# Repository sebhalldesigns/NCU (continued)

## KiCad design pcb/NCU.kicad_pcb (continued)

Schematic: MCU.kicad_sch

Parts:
C89: 100nF; C_0603_1608Metric_Pad1.08x0.95mm_HandSolder
C90, C92: 8.2pF; C_0603_1608Metric_Pad1.08x0.95mm_HandSolder
C91, C93: 5.1pF; C_0603_1608Metric_Pad1.08x0.95mm_HandSolder
D26: LED; LED_0603_1608Metric_Pad1.05x0.95mm_HandSolder
D27: SP0504BAHT; SOT-23-5
JP12: SolderJumper_2_Open; SolderJumper-2_P1.3mm_Open_RoundedPad1.0x1.5mm
R123, R125, R126: 10k; R_0603_1608Metric_Pad0.98x0.95mm_HandSolder
R124: 260R; R_0603_1608Metric_Pad0.98x0.95mm_HandSolder
TP18: BOOT; TestPoint_THTPad_D2.0mm_Drill1.0mm
U7: STM32H745ZITx; LQFP-144_20x20mm_P0.5mm
Y2: NX3215SA-32.768K-STD-MUS-2; NX3215SA32768KSTDMUS2; Mouser Part Number 344-NX3215SA32768K2
Y3: Crystal_GND24; NX2016SA32MEXS00ACS06465

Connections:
3V3: JP12.2 (B), R123.1, R126.1, U7.7 (VDD), U7.8 (VBAT), U7.13 (VDD), U7.16 (VDDSMPS), U7.19 (VDD), U7.32 (VDD), U7.42 (VDD), U7.56 (VDD), U7.71 (VDD), U7.79 (VDD), U7.90 (VDD50_USB), U7.91 (VDD33_USB), U7.92 (VDD), U7.106 (VDD), U7.119 (VDD), U7.129 (VDD), U7.144 (VDD); also elsewhere on the board
/CARD_SD/SD_CD: U7.99 (PA10); also elsewhere on the board
/CARD_SD/SD_CLK: U7.111 (SDMMC1_CK); also elsewhere on the board
/CARD_SD/SD_CMD: U7.114 (SDMMC1_CMD); also elsewhere on the board
/CARD_SD/SD_DAT0: U7.95 (SDMMC1_D0); also elsewhere on the board
/CARD_SD/SD_DAT1: U7.96 (SDMMC1_D1); also elsewhere on the board
/CARD_SD/SD_DAT2: U7.109 (SDMMC1_D2); also elsewhere on the board
/CARD_SD/SD_DAT3: U7.110 (SDMMC1_D3); also elsewhere on the board
/CONN_B/STM_SWDCLK: D27.3 (K), U7.107 (DEBUG_JTCK-SWCLK); also elsewhere on the board
/CONN_B/STM_SWDIO: D27.1 (K), U7.102 (DEBUG_JTMS-SWDIO); also elsewhere on the board
/CONN_B/STM_SWO: D27.5 (K), U7.130 (DEBUG_JTDO-SWO); also elsewhere on the board
/CONN_B/STM_USB_DM: U7.100 (USB_OTG_FS_DM); also elsewhere on the board
/CONN_B/STM_USB_DP: U7.101 (USB_OTG_FS_DP); also elsewhere on the board
/DRIVES/HSD0_CTRL: U7.82 (TIM4_CH1); also elsewhere on the board
/DRIVES/HSD1_CTRL: U7.83 (TIM4_CH2); also elsewhere on the board
/DRIVES/HSD01_EN: U7.81 (PD11); also elsewhere on the board
/DRIVES/HSD01_ISEN: U7.20 (ADC3_INP8); also elsewhere on the board
/DRIVES/HSD01_SEL: U7.21 (PF7); also elsewhere on the board
/DRIVES/HSD2_CTRL: U7.136 (TIM4_CH3); also elsewhere on the board
/DRIVES/HSD3_CTRL: U7.137 (TIM4_CH4); also elsewhere on the board
/DRIVES/HSD23_EN: U7.134 (PB7); also elsewhere on the board
/DRIVES/HSD23_ISEN: U7.22 (ADC3_INP7); also elsewhere on the board
/DRIVES/HSD23_SEL: U7.23 (PF9); also elsewhere on the board
/DRIVES/LSD0_CTRL: U7.59 (TIM1_CH1); also elsewhere on the board
/DRIVES/LSD0_STAT: U7.60 (PE10); also elsewhere on the board
/DRIVES/LSD1_CTRL: U7.61 (TIM1_CH2); also elsewhere on the board
/DRIVES/LSD1_STAT: U7.62 (PE12); also elsewhere on the board
/DRIVES/LSD2_CTRL: U7.63 (TIM1_CH3); also elsewhere on the board
/DRIVES/LSD2_STAT: U7.57 (PE7); also elsewhere on the board
/DRIVES/LSD3_CTRL: U7.64 (TIM1_CH4); also elsewhere on the board
/DRIVES/LSD3_STAT: U7.58 (PE8); also elsewhere on the board
/GPIO/GPIO0_IO: U7.43 (DAC1_OUT1); also elsewhere on the board
/GPIO/GPIO1_IO: U7.44 (DAC1_OUT2); also elsewhere on the board
/GPIO/GPIO2_IO: U7.37 (ADC1_INP16); also elsewhere on the board
/GPIO/GPIO3_IO: U7.38 (ADC1_INP17); also elsewhere on the board
/INPUTS/AIN0_IO: U7.40 (ADC1_INP15); also elsewhere on the board
/INPUTS/AIN1_IO: U7.45 (ADC1_INP3); also elsewhere on the board
/INPUTS/AIN2_IO: U7.50 (ADC1_INP5); also elsewhere on the board
/INPUTS/AIN3_IO: U7.28 (ADC1_INP10); also elsewhere on the board
/INPUTS/DIN0_IO: U7.30 (ADC3_INP0); also elsewhere on the board
/INPUTS/DIN1_IO: U7.31 (ADC3_INP1); also elsewhere on the board
/INPUTS/DIN2_IO: U7.24 (ADC3_INN2); also elsewhere on the board
/INPUTS/DIN3_IO: U7.52 (ADC1_INP2); also elsewhere on the board
/MCU/3V3_PG: U7.116 (PD4); also elsewhere on the board
/MCU/12V_IO: U7.53 (ADC2_INP6)
/MCU/A5V_PG: U7.117 (PD5); also elsewhere on the board
/MCU/CAN0_RX: U7.112 (FDCAN1_RX); also elsewhere on the board
/MCU/CAN0_TX: U7.113 (FDCAN1_TX); also elsewhere on the board
/MCU/CAN1_RX: U7.132 (FDCAN2_RX); also elsewhere on the board
/MCU/CAN1_TX: U7.133 (FDCAN2_TX); also elsewhere on the board
/MCU/ESP_SPI_CLK: U7.1 (SPI4_SCK); also elsewhere on the board
/MCU/ESP_SPI_CS: U7.3 (SPI4_NSS); also elsewhere on the board
/MCU/ESP_SPI_MISO: U7.4 (SPI4_MISO); also elsewhere on the board
/MCU/ESP_SPI_MOSI: U7.5 (SPI4_MOSI); also elsewhere on the board
/MCU/ETH_CRS_DV: U7.46 (ETH_CRS_DV); also elsewhere on the board
/MCU/ETH_INT: U7.49 (PB0); also elsewhere on the board
/MCU/ETH_MDC: U7.29 (ETH_MDC); also elsewhere on the board
/MCU/ETH_MDIO: U7.39 (ETH_MDIO); also elsewhere on the board
/MCU/ETH_RST: U7.108 (PA15); also elsewhere on the board
/MCU/ETH_RXD0: U7.47 (ETH_RXD0); also elsewhere on the board
/MCU/ETH_RXD1: U7.48 (ETH_RXD1); also elsewhere on the board
/MCU/ETH_TXD0: U7.72 (ETH_TXD0); also elsewhere on the board
/MCU/ETH_TXD1: U7.73 (ETH_TXD1); also elsewhere on the board
/MCU/ETH_TXEN: U7.67 (ETH_TX_EN); also elsewhere on the board
/MCU/LV_PG: U7.115 (PD3); also elsewhere on the board
/MCU/MCU Power/VDDLDO: U7.70 (VDDLDO), U7.105 (VDDLDO), U7.143 (VDDLDO); also elsewhere on the board
/MCU/PCIE_UART_CTS: U7.84 (UART8_CTS); also elsewhere on the board
/MCU/PCIE_UART_RTS: U7.85 (UART8_RTS); also elsewhere on the board
/MCU/PCIE_W_DISABLE: U7.120 (PD6); also elsewhere on the board
/MCU/RCC_OSC32_IN: C93.1, U7.10 (RCC_OSC32_IN), Y2.2
/MCU/RCC_OSC32_OUT: C91.1, U7.11 (RCC_OSC32_OUT), Y2.1
/MCU/RCC_OSC_IN: C92.1, U7.25 (RCC_OSC_IN), Y3.1
/MCU/RCC_OSC_OUT: C90.1, U7.26 (RCC_OSC_OUT), Y3.3
/MCU/STM_NRST: C89.1, D27.4 (K), R123.2, U7.27 (NRST); also elsewhere on the board
/MCU/VCAP: U7.68 (VCAP), U7.103 (VCAP), U7.140 (VCAP); also elsewhere on the board
/MCU/VFBSMPS: U7.17 (VFBSMPS); also elsewhere on the board
/MCU/VLXSMPS: U7.15 (VLXSMPS); also elsewhere on the board
/MCU/VREF+: U7.35 (VREF+), U7.36 (VDDA); also elsewhere on the board
/MOD_PCIE/UART_RX: U7.139 (UART8_TX); also elsewhere on the board
/MOD_PCIE/UART_TX: U7.138 (UART8_RX); also elsewhere on the board
GND: C89.2, C90.2, C91.2, C92.2, C93.2, D26.1 (K), D27.2 (A), R125.2, U7.6 (VSS), U7.12 (VSS), U7.14 (VSSSMPS), U7.18 (VSS), U7.33 (VSS), U7.34 (VSSA), U7.41 (VSS), U7.55 (VSS), U7.69 (VSS), U7.80 (VSS), U7.89 (VSS), U7.104 (VSS), U7.118 (VSS), U7.128 (VSS), U7.141 (VSS), Y3.2, Y3.4; also elsewhere on the board
unnamed: D26.2 (A), R124.2
unnamed: JP12.1 (A), R125.1, TP18.1, U7.135 (BOOT0)
unnamed: R126.2, U7.142 (PDR_ON)
unnamed: R124.1, U7.65 (PE15)
USB_VBUS: U7.98 (USB_OTG_FS_VBUS); also elsewhere on the board

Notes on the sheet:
Solder jumper for boot recovery - bridge to enter system bootloader mode

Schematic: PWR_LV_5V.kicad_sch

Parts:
C73, C74: 4.7uF; C_1210_3225Metric_Pad1.33x2.70mm_HandSolder
C75, C76: 0.1uF; C_0603_1608Metric_Pad1.08x0.95mm_HandSolder
C77: 33pF; C_0603_1608Metric_Pad1.08x0.95mm_HandSolder
C78, C79: 47uF; C_1210_3225Metric_Pad1.33x2.70mm_HandSolder
IC6: LMR51460SQDRRRQ1; SON50P300X300X80-13N-D; Manufacturer_Part_Number LMR51460SQDRRRQ1
L2: 4.7uH; L_Coilcraft_XAL7030-472
NT2: NetTie_2; NetTie-2_SMD_Pad0.5mm
R110: 19.1k; R_0603_1608Metric_Pad0.98x0.95mm_HandSolder
R111, R112: 100k; R_0603_1608Metric_Pad0.98x0.95mm_HandSolder
R113: 1k; R_0603_1608Metric_Pad0.98x0.95mm_HandSolder

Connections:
3V3: R111.2; also elsewhere on the board
12V_PRT: C73.1, C74.1, C75.1, IC6.9 (EN), IC6.10 (VIN_1), IC6.11 (VIN_2), IC6.12 (VIN_3); also elsewhere on the board
/MCU/LV_PG: IC6.5 (PG), R111.1; also elsewhere on the board
/PWR/PWR_LV_5V/LMR_FB: C77.2, IC6.7 (FB), R110.1, R112.2
/PWR/PWR_LV_5V/LMR_SW: C76.1, IC6.1 (SW_1), IC6.2 (SW_2), IC6.3 (SW_3), L2.1
GND: C73.2, C74.2, C75.2, C78.2, C79.2, IC6.13 (PGND/DAP), NT2.1; also elsewhere on the board
LV_5V: C78.1, C79.1, L2.2, R112.1, R113.1; also elsewhere on the board
unnamed: C77.1, R113.2
unnamed: IC6.8 (AGND), NT2.2, R110.2
unnamed: C76.2, IC6.4 (BOOT)

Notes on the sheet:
12V-5V Supply Place near to 12V input

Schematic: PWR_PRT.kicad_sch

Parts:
D25: SBR2065D1-13; SBR2065D113; Mouser Part Number 621-SBR2065D1-13
U6: TA6F27CA; D_SOD-128

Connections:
12V: D25.1 (A_1), D25.3 (A_2); also elsewhere on the board
12V_PRT: D25.2 (COM_K), U6.2; also elsewhere on the board
GND: U6.1; also elsewhere on the board

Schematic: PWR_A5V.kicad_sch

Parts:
C86, C87: 1uF; C_0603_1608Metric_Pad1.08x0.95mm_HandSolder
IC8: LP2951-50DRG4; SOIC127P600X175-8N; Mouser Part Number 595-LP2951-50DRG4
R118: 100k; R_0603_1608Metric_Pad0.98x0.95mm_HandSolder

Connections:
3V3: R118.2; also elsewhere on the board
12V_PRT: C86.1, IC8.8 (INPUT); also elsewhere on the board
/MCU/A5V_PG: IC8.5 (~ERROR), R118.1; also elsewhere on the board
A5V: C87.1, IC8.1 (OUTPUT), IC8.2 (SENSE); also elsewhere on the board
GND: C86.2, C87.2, IC8.3 (SHUTDOWN), IC8.4 (GND); also elsewhere on the board
unnamed: IC8.6 (VTAP), IC8.7 (FEEDBACK)

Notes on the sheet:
A5V Analog power supply

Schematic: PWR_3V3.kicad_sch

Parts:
C80: 4.7nF; C_0603_1608Metric_Pad1.08x0.95mm_HandSolder
C81: 22uF; C_0603_1608Metric_Pad1.08x0.95mm_HandSolder
C82: 10pF; C_0603_1608Metric_Pad1.08x0.95mm_HandSolder
C83, C84: 22uF; L_1206_3216Metric_Pad1.22x1.90mm_HandSolder
C85: 10uF; C_0603_1608Metric_Pad1.08x0.95mm_HandSolder
IC7: TPS628101HQWRWYRQ1; TPS6281008QWRWYRQ1; Mouser Part Number TPS628101HQWRWYRQ1
L3: 0.47uH; XFL4012
R114: 100k; R_0603_1608Metric_Pad0.98x0.95mm_HandSolder
R115: 8.06k; R_0603_1608Metric_Pad0.98x0.95mm_HandSolder
R116: 88.7k; R_0603_1608Metric_Pad0.98x0.95mm_HandSolder
R117: 19.6k; R_0603_1608Metric_Pad0.98x0.95mm_HandSolder

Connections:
3V3: C82.1, C83.1, C84.1, C85.1, L3.2, R114.2, R116.2; also elsewhere on the board
5V: C81.1, IC7.1 (MODE/SYNC_1), IC7.2 (VIN), IC7.8 (EN_1), IC7.10 (MODE/SYNC_2), IC7.13 (EN_2); also elsewhere on the board
/MCU/3V3_PG: IC7.9 (PG), R114.1; also elsewhere on the board
/PWR/PWR_3V3/TPS_CF: IC7.7 (COMP/_FSET_1), IC7.12 (COMP/_FSET_2), R115.2
/PWR/PWR_3V3/TPS_FB: C82.2, IC7.5 (FB_1), IC7.11 (FB_2), R116.1, R117.2
GND: C80.2, C81.2, C83.2, C84.2, C85.2, IC7.4 (GND), R115.1, R117.1; also elsewhere on the board
unnamed: C80.1, IC7.6 (SS/TR)
unnamed: IC7.3 (SW), L3.1

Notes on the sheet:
3V3 Supply Place away from 12V supply

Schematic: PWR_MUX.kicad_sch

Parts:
C88: 1u; C_0603_1608Metric_Pad1.08x0.95mm_HandSolder
C96: 1u; C_0603_1608Metric
C97: 100n; C_0603_1608Metric
IC9: TPS2121RUXT; Mouser Part Number 595-TPS2121RUXT
JP11: SolderJumper_2_Bridged; SolderJumper-2_P1.3mm_Bridged_RoundedPad1.0x1.5mm
R119, R121: 18k; R_0603_1608Metric_Pad0.98x0.95mm_HandSolder
R120: 5k; R_0603_1608Metric_Pad0.98x0.95mm_HandSolder
R122: 22.1k; R_0603_1608Metric_Pad0.98x0.95mm_HandSolder

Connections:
3V3: R121.1; also elsewhere on the board
5V: IC9.1 (OUT_1), IC9.8 (OUT_2); also elsewhere on the board
/MCU/PCIE_W_DISABLE: IC9.9 (ST), R121.2; also elsewhere on the board
GND: C88.2, C96.2, C97.2, IC9.4 (OV2), IC9.5 (OV1), IC9.12 (GND), JP11.2 (B), R120.2, R122.2; also elsewhere on the board
LV_5V: IC9.7 (IN1), R119.1; also elsewhere on the board
unnamed: IC9.3 (CP2), JP11.1 (A)
unnamed: IC9.10 (ILIM), R122.1
unnamed: IC9.6 (PR1), R119.2, R120.1
unnamed: C88.1, IC9.11 (SS)
USB_VBUS: C96.1, C97.1, IC9.2 (IN2); also elsewhere on the board

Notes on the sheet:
Ideally place these near the connector

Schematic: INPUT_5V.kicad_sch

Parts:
C12: 100nF; C_0603_1608Metric_Pad1.08x0.95mm_HandSolder
D6: BAT54S; SOT-23
R17: 1k; R_0603_1608Metric_Pad0.98x0.95mm_HandSolder
R18: 1.5k; R_0603_1608Metric_Pad0.98x0.95mm_HandSolder
R19: 100; R_0603_1608Metric_Pad0.98x0.95mm_HandSolder

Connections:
3V3: D6.2 (K); also elsewhere on the board
/CONN_A/AIN_1: R17.1; also elsewhere on the board
/INPUTS/AIN1_IO: C12.1, D6.3, R19.2; also elsewhere on the board
GND: C12.2, D6.1 (A), R18.2; also elsewhere on the board
unnamed: R17.2, R18.1, R19.1

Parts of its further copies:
C48, C50, C51: 100nF; C_0603_1608Metric_Pad1.08x0.95mm_HandSolder
D11, D14, D15: BAT54S; SOT-23
R39, R47, R50: 1k; R_0603_1608Metric_Pad0.98x0.95mm_HandSolder
R40, R48, R51: 1.5k; R_0603_1608Metric_Pad0.98x0.95mm_HandSolder
R42, R49, R52: 100; R_0603_1608Metric_Pad0.98x0.95mm_HandSolder

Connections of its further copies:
3V3: D11.2 (K), D14.2 (K), D15.2 (K); also elsewhere on the board
/CONN_A/AIN_0: R47.1; also elsewhere on the board
/CONN_A/AIN_2: R39.1; also elsewhere on the board
/CONN_A/AIN_3: R50.1; also elsewhere on the board
/INPUTS/AIN0_IO: C50.1, D14.3, R49.2; also elsewhere on the board
/INPUTS/AIN2_IO: C48.1, D11.3, R42.2; also elsewhere on the board
/INPUTS/AIN3_IO: C51.1, D15.3, R52.2; also elsewhere on the board
GND: C48.2, C50.2, C51.2, D11.1 (A), D14.1 (A), D15.1 (A), R40.2, R48.2, R51.2; also elsewhere on the board
unnamed: R39.2, R40.1, R42.1
unnamed: R47.2, R48.1, R49.1
unnamed: R50.2, R51.1, R52.1

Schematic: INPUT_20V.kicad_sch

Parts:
C52: 100nF; C_0603_1608Metric_Pad1.08x0.95mm_HandSolder
D16: BAT54S; SOT-23
R53: 8.2k; R_0603_1608Metric_Pad0.98x0.95mm_HandSolder
R54: 1k; R_0603_1608Metric_Pad0.98x0.95mm_HandSolder
R55: 100; R_0603_1608Metric_Pad0.98x0.95mm_HandSolder

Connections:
3V3: D16.2 (K); also elsewhere on the board
/CONN_A/DIN_1: R53.1; also elsewhere on the board
/INPUTS/DIN1_IO: C52.1, D16.3, R55.2; also elsewhere on the board
GND: C52.2, D16.1 (A), R54.2; also elsewhere on the board
unnamed: R53.2, R54.1, R55.1

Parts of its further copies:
C53, C56, C63, C64: 100nF; C_0603_1608Metric_Pad1.08x0.95mm_HandSolder
D17, D18, D19, D21: BAT54S; SOT-23
R56, R63, R74, R81: 8.2k; R_0603_1608Metric_Pad0.98x0.95mm_HandSolder
R57, R64, R75, R82: 1k; R_0603_1608Metric_Pad0.98x0.95mm_HandSolder
R58, R67, R77, R83: 100; R_0603_1608Metric_Pad0.98x0.95mm_HandSolder

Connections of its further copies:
3V3: D17.2 (K), D18.2 (K), D19.2 (K), D21.2 (K); also elsewhere on the board
12V_PRT: R81.1; also elsewhere on the board
/CONN_A/DIN_0: R63.1; also elsewhere on the board
/CONN_A/DIN_2: R56.1; also elsewhere on the board
/CONN_A/DIN_3: R74.1; also elsewhere on the board
/INPUTS/12V_IO: C64.1, D21.3, R83.2
/INPUTS/DIN0_IO: C56.1, D18.3, R67.2; also elsewhere on the board
/INPUTS/DIN2_IO: C53.1, D17.3, R58.2; also elsewhere on the board
/INPUTS/DIN3_IO: C63.1, D19.3, R77.2; also elsewhere on the board
GND: C53.2, C56.2, C63.2, C64.2, D17.1 (A), D18.1 (A), D19.1 (A), D21.1 (A), R57.2, R64.2, R75.2, R82.2; also elsewhere on the board
unnamed: R56.2, R57.1, R58.1
unnamed: R63.2, R64.1, R67.1
unnamed: R74.2, R75.1, R77.1
unnamed: R81.2, R82.1, R83.1

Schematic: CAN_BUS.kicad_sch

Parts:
C66: 1u; C_0603_1608Metric
C67: 100n; C_0603_1608Metric
IC3: ESD2CAN24DBZRQ1; SOT95P237X112-3N; Mouser Part Number 595-ESD2CAN24DBZRQ1
R85: 120R; R_0603_1608Metric_Pad0.98x0.95mm_HandSolder; not fitted
TP14: CAN_H; TestPoint_THTPad_D2.0mm_Drill1.0mm
TP15: CAN_L; TestPoint_THTPad_D2.0mm_Drill1.0mm
U4: SN65HVD230; SOIC-8_3.9x4.9mm_P1.27mm

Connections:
3V3: C66.1, C67.1, U4.3 (VCC); also elsewhere on the board
/CONN_A/CAN1_H: IC3.2 (IO_2), R85.1, TP14.1, U4.7 (CANH); also elsewhere on the board
/CONN_A/CAN1_L: IC3.1 (IO_1), R85.2, TP15.1, U4.6 (CANL); also elsewhere on the board
/MCU/CAN1_RX: U4.4 (R); also elsewhere on the board
/MCU/CAN1_TX: U4.1 (D); also elsewhere on the board
GND: C66.2, C67.2, IC3.3 (GND), U4.2 (GND), U4.8 (Rs); also elsewhere on the board

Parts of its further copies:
C71: 1u; C_0603_1608Metric
C72: 100n; C_0603_1608Metric
IC5: ESD2CAN24DBZRQ1; SOT95P237X112-3N; Mouser Part Number 595-ESD2CAN24DBZRQ1
R109: 120R; R_0603_1608Metric_Pad0.98x0.95mm_HandSolder; not fitted
TP16: CAN_H; TestPoint_THTPad_D2.0mm_Drill1.0mm
TP17: CAN_L; TestPoint_THTPad_D2.0mm_Drill1.0mm
U5: SN65HVD230; SOIC-8_3.9x4.9mm_P1.27mm

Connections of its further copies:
3V3: C71.1, C72.1, U5.3 (VCC); also elsewhere on the board
/CONN_A/CAN0_H: IC5.2 (IO_2), R109.1, TP16.1, U5.7 (CANH); also elsewhere on the board
/CONN_A/CAN0_L: IC5.1 (IO_1), R109.2, TP17.1, U5.6 (CANL); also elsewhere on the board
/MCU/CAN0_RX: U5.4 (R); also elsewhere on the board
/MCU/CAN0_TX: U5.1 (D); also elsewhere on the board
GND: C71.2, C72.2, IC5.3 (GND), U5.2 (GND), U5.8 (Rs); also elsewhere on the board

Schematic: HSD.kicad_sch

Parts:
C42: 10u; C_0603_1608Metric
C43: 100n; C_0603_1608Metric
D7: 1N4148W; D_SOD-123
IC1: VND7E025AJTR; SOP50P600X170-17N; Mouser Part Number 511-VND7E025AJTR
R24, R25: 100k; R_0603_1608Metric_Pad0.98x0.95mm_HandSolder
R26, R27, R28, R29, R30, R33: 15k; R_0603_1608Metric_Pad0.98x0.95mm_HandSolder
R31: 620R; R_0603_1608Metric_Pad0.98x0.95mm_HandSolder
R32: 4.7k; R_0603_1608Metric_Pad0.98x0.95mm_HandSolder

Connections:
3V3: R33.1; also elsewhere on the board
12V_PRT: C42.1, C43.1, IC1.17 (VCC); also elsewhere on the board
/CONN_A/HSD_2: IC1.13 (OUTPUT0_1), IC1.14 (OUTPUT0_2), IC1.15 (OUTPUT0_3), IC1.16 (OUTPUT0_4); also elsewhere on the board
/CONN_A/HSD_3: IC1.9 (OUTPUT1_1), IC1.10 (OUTPUT1_2), IC1.11 (OUTPUT1_3), IC1.12 (OUTPUT1_4); also elsewhere on the board
/DRIVES/HSD2_CTRL: R24.1, R26.1; also elsewhere on the board
/DRIVES/HSD3_CTRL: R25.1, R30.1; also elsewhere on the board
/DRIVES/HSD23_EN: R27.1; also elsewhere on the board
/DRIVES/HSD23_ISEN: R29.1; also elsewhere on the board
/DRIVES/HSD23_SEL: R28.1; also elsewhere on the board
GND: C42.2, C43.2, D7.1 (K), R24.2, R25.2, R31.1, R32.2; also elsewhere on the board
unnamed: D7.2 (A), IC1.4 (GND), R32.1
unnamed: IC1.7 (CS), R29.2, R31.2
unnamed: IC1.1 (INPUT0), R26.2
unnamed: IC1.8 (INPUT1), R30.2
unnamed: IC1.5 (SEL0), R28.2
unnamed: IC1.3 (SEN), R27.2
unnamed: IC1.2 (~FAULTRST), R33.2

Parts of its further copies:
C68: 10u; C_0603_1608Metric
C69: 100n; C_0603_1608Metric
D23: 1N4148W; D_SOD-123
IC4: VND7E025AJTR; SOP50P600X170-17N; Mouser Part Number 511-VND7E025AJTR
R94, R95: 100k; R_0603_1608Metric_Pad0.98x0.95mm_HandSolder
R96, R97, R98, R99, R100, R103: 15k; R_0603_1608Metric_Pad0.98x0.95mm_HandSolder
R101: 620R; R_0603_1608Metric_Pad0.98x0.95mm_HandSolder
R102: 4.7k; R_0603_1608Metric_Pad0.98x0.95mm_HandSolder

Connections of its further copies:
3V3: R103.1; also elsewhere on the board
12V_PRT: C68.1, C69.1, IC4.17 (VCC); also elsewhere on the board
/CONN_A/HSD_0: IC4.13 (OUTPUT0_1), IC4.14 (OUTPUT0_2), IC4.15 (OUTPUT0_3), IC4.16 (OUTPUT0_4); also elsewhere on the board
/CONN_A/HSD_1: IC4.9 (OUTPUT1_1), IC4.10 (OUTPUT1_2), IC4.11 (OUTPUT1_3), IC4.12 (OUTPUT1_4); also elsewhere on the board
/DRIVES/HSD0_CTRL: R94.1, R96.1; also elsewhere on the board
/DRIVES/HSD1_CTRL: R95.1, R100.1; also elsewhere on the board
/DRIVES/HSD01_EN: R97.1; also elsewhere on the board
/DRIVES/HSD01_ISEN: R99.1; also elsewhere on the board
/DRIVES/HSD01_SEL: R98.1; also elsewhere on the board
GND: C68.2, C69.2, D23.1 (K), R94.2, R95.2, R101.1, R102.2; also elsewhere on the board
unnamed: D23.2 (A), IC4.4 (GND), R102.1
unnamed: IC4.7 (CS), R99.2, R101.2
unnamed: IC4.1 (INPUT0), R96.2
unnamed: IC4.8 (INPUT1), R100.2
unnamed: IC4.5 (SEL0), R98.2
unnamed: IC4.3 (SEN), R97.2
unnamed: IC4.2 (~FAULTRST), R103.2

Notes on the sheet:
RSENSE calculation: K given as 2950, chose 15A Imax: RSENSE = 3.0/(15/2950) = 590 ohms. Closest normal value is 620R. the 3.0 is the target ADC voltage for Imax

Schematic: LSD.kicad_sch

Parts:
R20, R21: 2.2k; R_0603_1608Metric_Pad0.98x0.95mm_HandSolder
R22, R23: 100k; R_0603_1608Metric_Pad0.98x0.95mm_HandSolder
S1: BTS3050EJXUMA1; SOIC127P600X115-9N; Mouser Part Number 726-BTS3050EJXUMA1

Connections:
3V3: R23.1; also elsewhere on the board
/CONN_A/LSD_1: S1.9 (EP); also elsewhere on the board
/DRIVES/LSD1_CTRL: R20.2; also elsewhere on the board
/DRIVES/LSD1_STAT: R21.2; also elsewhere on the board
GND: R22.2, S1.6 (GND_1), S1.7 (GND_2), S1.8 (GND_3); also elsewhere on the board
unnamed: R20.1, R22.1, S1.1 (IN)
unnamed: R21.1, R23.2, S1.3 (STATUS)

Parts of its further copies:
R86, R87, R90, R91, R104, R105: 2.2k; R_0603_1608Metric_Pad0.98x0.95mm_HandSolder
R88, R89, R92, R93, R106, R107: 100k; R_0603_1608Metric_Pad0.98x0.95mm_HandSolder
S2, S3, S4: BTS3050EJXUMA1; SOIC127P600X115-9N; Mouser Part Number 726-BTS3050EJXUMA1

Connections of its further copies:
3V3: R89.1, R93.1, R107.1; also elsewhere on the board
/CONN_A/LSD_0: S2.9 (EP); also elsewhere on the board
/CONN_A/LSD_2: S3.9 (EP); also elsewhere on the board
/CONN_A/LSD_3: S4.9 (EP); also elsewhere on the board
/DRIVES/LSD0_CTRL: R86.2; also elsewhere on the board
/DRIVES/LSD0_STAT: R87.2; also elsewhere on the board
/DRIVES/LSD2_CTRL: R90.2; also elsewhere on the board
/DRIVES/LSD2_STAT: R91.2; also elsewhere on the board
/DRIVES/LSD3_CTRL: R104.2; also elsewhere on the board
/DRIVES/LSD3_STAT: R105.2; also elsewhere on the board
GND: R88.2, R92.2, R106.2, S2.6 (GND_1), S2.7 (GND_2), S2.8 (GND_3), S3.6 (GND_1), S3.7 (GND_2), S3.8 (GND_3), S4.6 (GND_1), S4.7 (GND_2), S4.8 (GND_3); also elsewhere on the board
unnamed: R86.1, R88.1, S2.1 (IN)
unnamed: R87.1, R89.2, S2.3 (STATUS)
unnamed: R90.1, R92.1, S3.1 (IN)
unnamed: R91.1, R93.2, S3.3 (STATUS)
unnamed: R104.1, R106.1, S4.1 (IN)
unnamed: R105.1, R107.2, S4.3 (STATUS)

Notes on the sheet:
Rin calculated by VOHuC(max)/IIN(max). Iinmax is 2mA and VOHuCmax is 3v3. Therefore Rin(min) is 1.6kOhm min. Choosing 2.2k

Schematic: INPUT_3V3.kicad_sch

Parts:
C44: 100nF; C_0603_1608Metric_Pad1.08x0.95mm_HandSolder
D8: BAT54S; SOT-23
R34: 100; R_0603_1608Metric_Pad0.98x0.95mm_HandSolder

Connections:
3V3: D8.2 (K); also elsewhere on the board
/CONN_B/GPIO_1: R34.1; also elsewhere on the board
/GPIO/GPIO1_IO: C44.1, D8.3, R34.2; also elsewhere on the board
GND: C44.2, D8.1 (A); also elsewhere on the board

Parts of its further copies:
C45, C65, C70: 100nF; C_0603_1608Metric_Pad1.08x0.95mm_HandSolder
D9, D22, D24: BAT54S; SOT-23
R35, R84, R108: 100; R_0603_1608Metric_Pad0.98x0.95mm_HandSolder

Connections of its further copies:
3V3: D9.2 (K), D22.2 (K), D24.2 (K); also elsewhere on the board
/CONN_B/GPIO_0: R108.1; also elsewhere on the board
/CONN_B/GPIO_2: R35.1; also elsewhere on the board
/CONN_B/GPIO_3: R84.1; also elsewhere on the board
/GPIO/GPIO0_IO: C70.1, D24.3, R108.2; also elsewhere on the board
/GPIO/GPIO2_IO: C45.1, D9.3, R35.2; also elsewhere on the board
/GPIO/GPIO3_IO: C65.1, D22.3, R84.2; also elsewhere on the board
GND: C45.2, C65.2, C70.2, D9.1 (A), D22.1 (A), D24.1 (A); also elsewhere on the board

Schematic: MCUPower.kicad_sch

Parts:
C13: 4.7uF; C_0603_1608Metric_Pad1.08x0.95mm_HandSolder
C14, C15, C16, C18, C19, C20, C21, C23, C25, C26, C27, C28, C29, C30, C31, C36, C38, C40, C41: 100nF; C_0603_1608Metric_Pad1.08x0.95mm_HandSolder
C17, C33, C39: 1uF; C_0603_1608Metric_Pad1.08x0.95mm_HandSolder
C22, C24, C34: 10uF; C_0603_1608Metric_Pad1.08x0.95mm_HandSolder
C32: 220pF; C_0603_1608Metric_Pad1.08x0.95mm_HandSolder
C35, C37: 2.2uF; C_0603_1608Metric_Pad1.08x0.95mm_HandSolder
FB2: FCM 1608KF-471T03; L_0603_1608Metric_Pad1.05x0.95mm_HandSolder
JP6, JP7: SolderJumper_2_Bridged; SolderJumper-2_P1.3mm_Bridged_RoundedPad1.0x1.5mm
L1: 2.2uH; L_0805_2012Metric_Pad1.05x1.20mm_HandSolder

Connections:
3V3: C13.1, C14.1, C15.1, C16.1, C17.1, C18.1, C19.1, C20.1, C21.1, C22.1, C23.1, C24.1, C25.1, C26.1, C27.1, C28.1, C29.1, C30.1, C31.1, FB2.1; also elsewhere on the board
/MCU/MCU Power/1V2_MCU: C34.1, JP6.1 (A), L1.2
/MCU/MCU Power/VDDLDO: C38.1, C40.1, JP6.2 (B); also elsewhere on the board
/MCU/VCAP: C35.1, C37.1, JP7.1 (A); also elsewhere on the board
/MCU/VFBSMPS: JP7.2 (B); also elsewhere on the board
/MCU/VLXSMPS: C32.1, L1.1; also elsewhere on the board
/MCU/VREF+: C33.1, C36.1, C39.1, C41.1, FB2.2; also elsewhere on the board
GND: C13.2, C14.2, C15.2, C16.2, C17.2, C18.2, C19.2, C20.2, C21.2, C22.2, C23.2, C24.2, C25.2, C26.2, C27.2, C28.2, C29.2, C30.2, C31.2, C32.2, C33.2, C34.2, C35.2, C36.2, C37.2, C38.2, C39.2, C40.2, C41.2; also elsewhere on the board

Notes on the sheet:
AKA VFBSD
AKA VDD_SMPS_OUT Output from switching converter
AKA VDD_SMPS_IN Input supply to switching converter
Analog references
Both caps placed near VDD33USB
This should be a copper pour possibly under the STM on the power layer

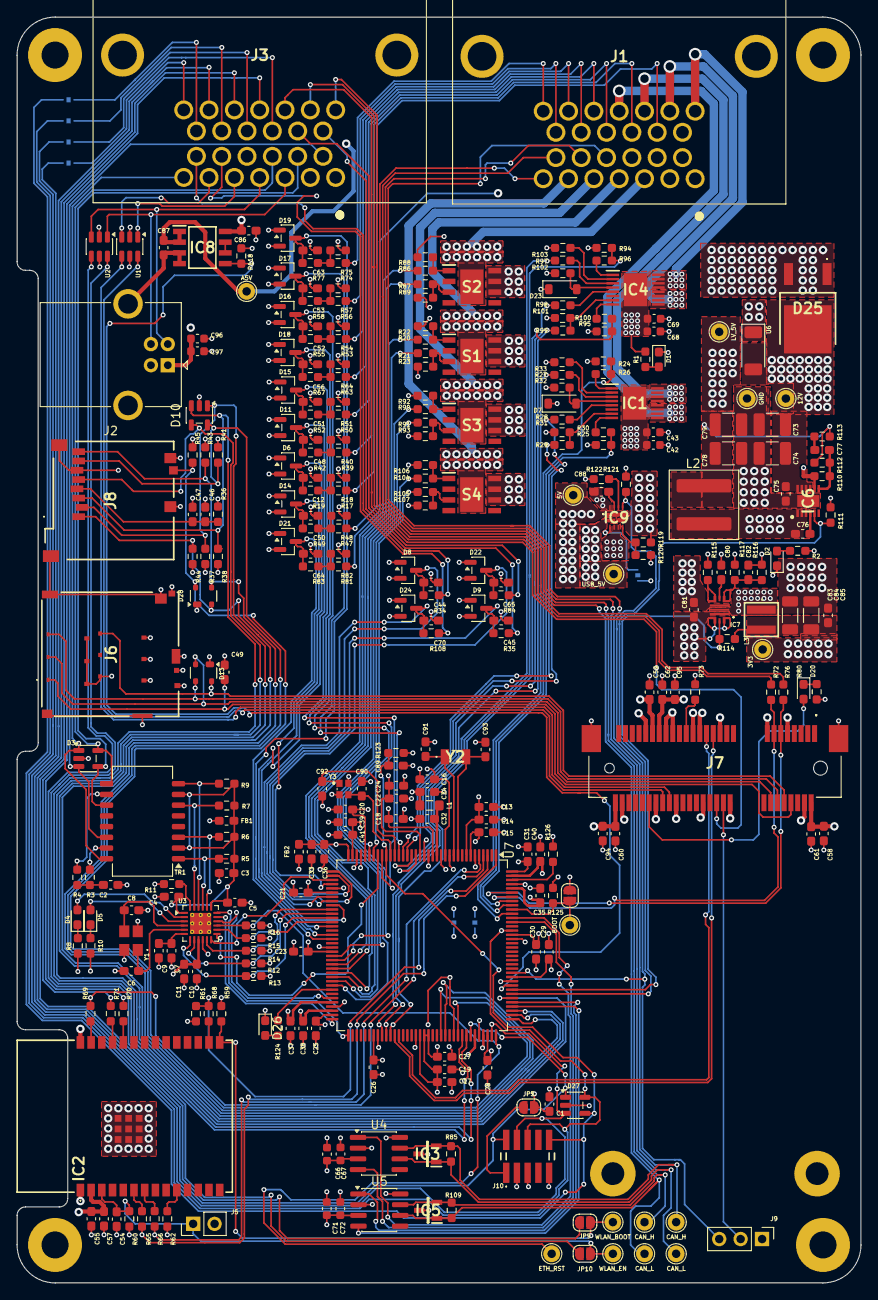
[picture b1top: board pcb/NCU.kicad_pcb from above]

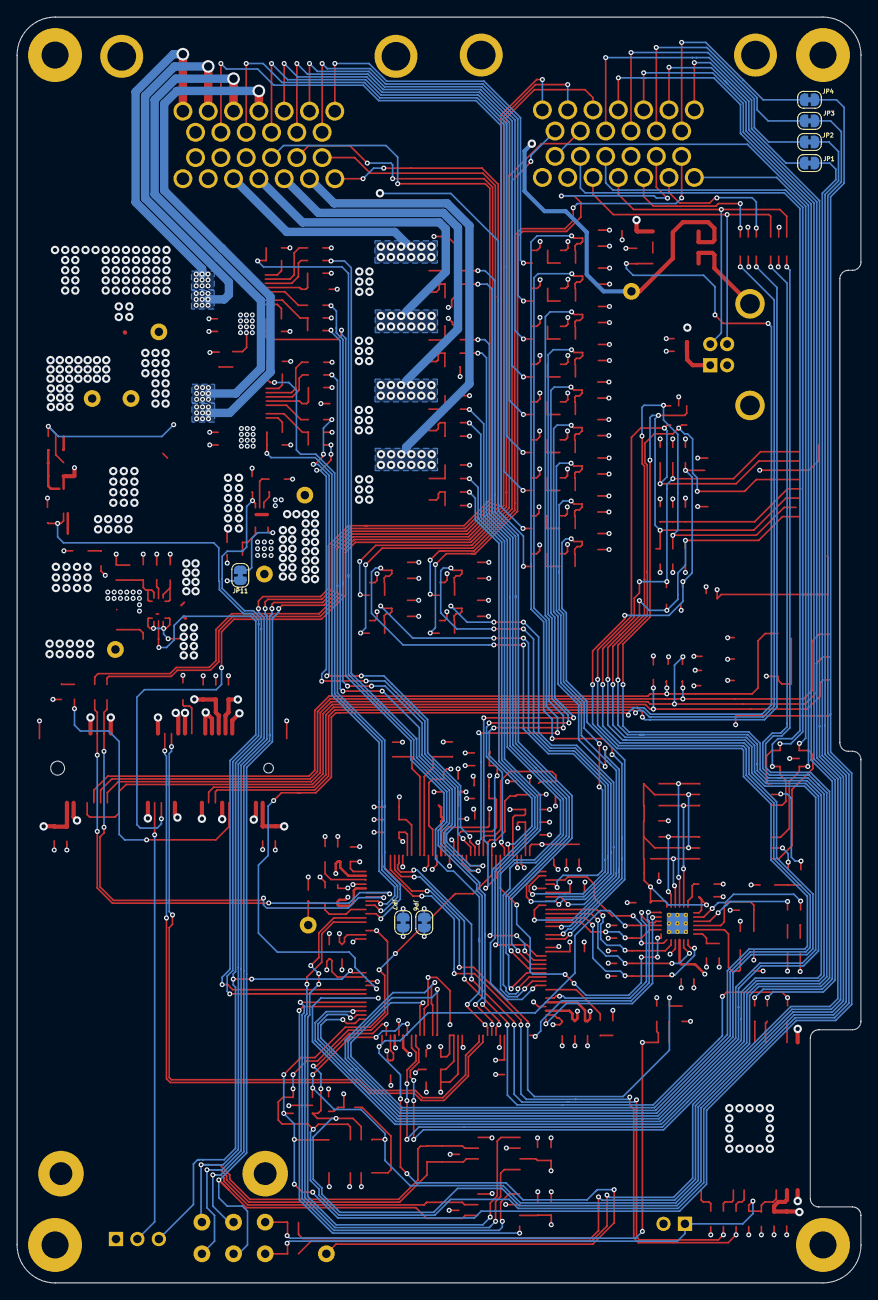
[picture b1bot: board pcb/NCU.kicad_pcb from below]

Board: 4 copper layers, 100.0 x 150.0 mm, 318 parts (7 on the bottom side), 219 nets.
